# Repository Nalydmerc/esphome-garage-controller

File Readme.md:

### ESPHome Garage Door Controller

I am a forgetful man. I forget to close the garage door. My wife gets frustrated that I forget to close the garage door. I may or may not get slightly banned from the garage due to leaving the garage door open too many times after leaving for work. So, I do what any sensible man would do. I offload my responsibilities to technology, of course.

The device uses an ESP8266 running ESPHome to connect to HomeAssistant and do garage door things. I used a hall effect sensor to detect if each door was open or closed, but you could use any contact that opens/closes depending on the state of the door. To open and close the doors, I just wired in a relay in parallel with each button. YMMV, but for mine this did mean I had to physically disassemble each button and solder extra wires onto the PCB.

This project was designed to be cheap, as opposed to involved. You can build your own buck converters into your projects (I have in the past), but at the end of the day it's still cheaper to buy one of those cheap adjustable converters on aliexpress and call it a day. Sure there's 0.4V of switching noise, but the D1 Mini has a built in LDO anyway, as do most cheap development boards. ¯\\\_(ツ)\_/¯ A good project is one that is finished to spec, and my spec is that it works.

### Mechanical Assembly and Bill of Materials

.step files for a 3D printed enclosure are included in this project. The backplate uses M3 screws to mount the PCB, and M4 screws to attach the top. Other Non-PCB materials are as follows:

|Item | Qty|Link |
|--|--|--|
| Hall effect sensor |2| https://www.aliexpress.us/item/3256805925218267.html |
| Cabling || https://www.aliexpress.us/item/3256806428440404.html |
|Wire Ferrules (for crimping ends) || https://www.aliexpress.us/item/3256805075641713.html |
| Lever-nut connectors (love these) || https://www.aliexpress.us/item/3256803684080411.html |
| M3 Brass Inserts | 4 | https://www.aliexpress.us/item/3256803396040989.html |
| M3x5mm |4||
| M4 Brass Inserts | 4 | https://www.aliexpress.us/item/3256803396040989.html |
| M4x35mm |4||

### Manufacturing the PCB

If you want to make this PCB yourself, simply zip up the outputs folder and upload it to the PCB manufacturer of your choice. You can take the bill of materials CSV and upload it directly to digikey to create a cart with the needed components. Anything that doesn't have a digikey part number, I listed the relevant aliexpress product page.

### Random notes for myself

Reminder: Set switches to pins 5 and 4 to prevent them from toggling during startup. (esp8266s are weird. Never before have I had to deal with GPIOs just doing random things during the startup process.)

https://community.home-assistant.io/t/esp8266-relay-active-low-how-to-prevent-triggering-on-boot-or-reset-solved/88279/30
https://rabbithole.wwwdotorg.org/2017/03/28/esp8266-gpio.html

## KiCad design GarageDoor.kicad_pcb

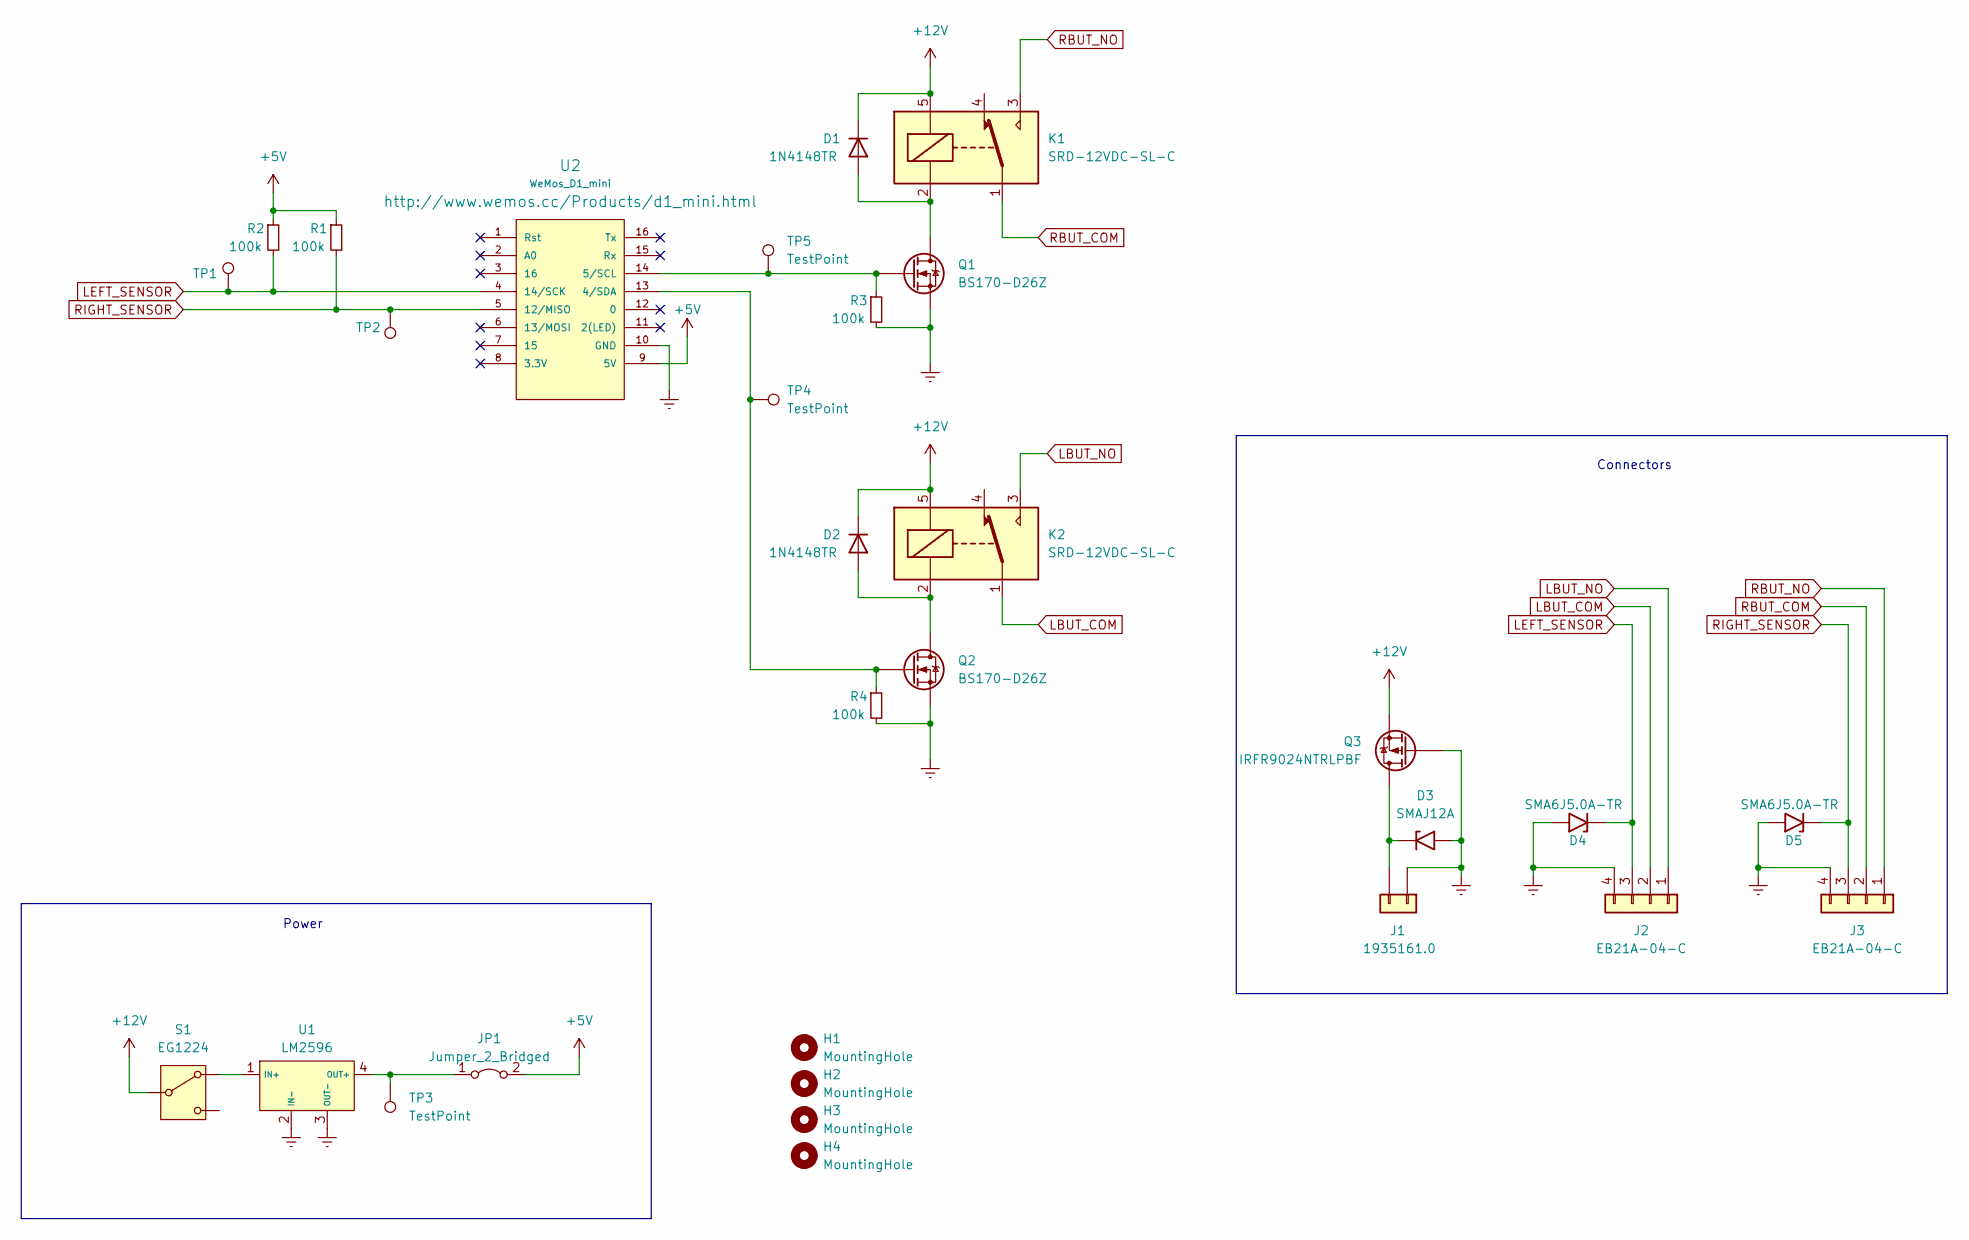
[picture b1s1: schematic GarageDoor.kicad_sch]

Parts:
D1, D2: 1N4148TR; D_DO-35_SOD27_P10.16mm_Horizontal; Digikey PN 1N4148FSCT-ND
D3: SMAJ12A; D_SMA_Handsoldering; Digikey PN SMAJ12ALFCT-ND
D4, D5: SMA6J5.0A-TR; D_SMA_Handsoldering; Digikey PN 497-5938-1-ND
H1, H2, H3, H4: MountingHole; MountingHole_3.2mm_M3
J1: 1935161.0; TerminalBlock_bornier-2_P5.08mm
J2, J3: EB21A-04-C; TerminalBlock_bornier-4_P5.08mm
JP1: Jumper_2_Bridged; PinHeader_1x02_P2.54mm_Vertical; Digikey PN S9337-ND
K1, K2: SRD-12VDC-SL-C; Relay_SPDT_Songle
Q1, Q2: BS170-D26Z; TO-92_Inline_Wide; Digikey PN BS170-D26ZCT-ND
Q3: IRFR9024NTRLPBF; TO-252-2; Digikey PN IRFR9024NTRLPBFCT-ND
R1, R2, R3, R4: 100k; R_Axial_DIN0207_L6.3mm_D2.5mm_P15.24mm_Horizontal
S1: EG1224; SW_E-Switch_EG1224_SPDT_Angled; Digikey PN EG2585-ND
TP1, TP2, TP3, TP4, TP5: TestPoint; TestPoint_Pad_1.5x1.5mm
U1: LM2596; LM2596Module
U2: WeMos_D1_mini; wemos-d1-mini-with-pin-header-and-connector

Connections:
+5V: JP1.2 (B), R1.1, R2.1, U2.9 (5V)
+12V: D1.1 (K), D2.1 (K), K1.5, K2.5, Q3.3 (S), S1.2 (B)
Earth: D3.2 (A2), D4.2 (A2), D5.2 (A2), J1.1, J2.4, J3.4, Q1.3 (S), Q2.3 (S), Q3.1 (G), R3.2, R4.2, U1.2 (IN-), U1.3 (OUT-), U2.10 (GND)
LBUT_COM: J2.2, K2.1
LBUT_NO: J2.1, K2.3
LEFT_SENSOR: D4.1 (A1), J2.3, R2.2, TP1.1, U2.4 (14/SCK)
unnamed: D1.2 (A), K1.2, Q1.1 (D)
unnamed: D2.2 (A), K2.2, Q2.1 (D)
unnamed: D3.1 (A1), J1.2, Q3.2 (D)
unnamed: JP1.1 (A), TP3.1, U1.4 (OUT+)
unnamed: Q1.2 (G), R3.1, TP5.1, U2.14 (5/SCL)
unnamed: Q2.2 (G), R4.1, TP4.1, U2.13 (4/SDA)
unnamed: S1.3 (A), U1.1 (IN+)
RBUT_COM: J3.2, K1.1
RBUT_NO: J3.1, K1.3
RIGHT_SENSOR: D5.1 (A1), J3.3, R1.2, TP2.1, U2.5 (12/MISO)

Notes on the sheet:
Connectors
Power

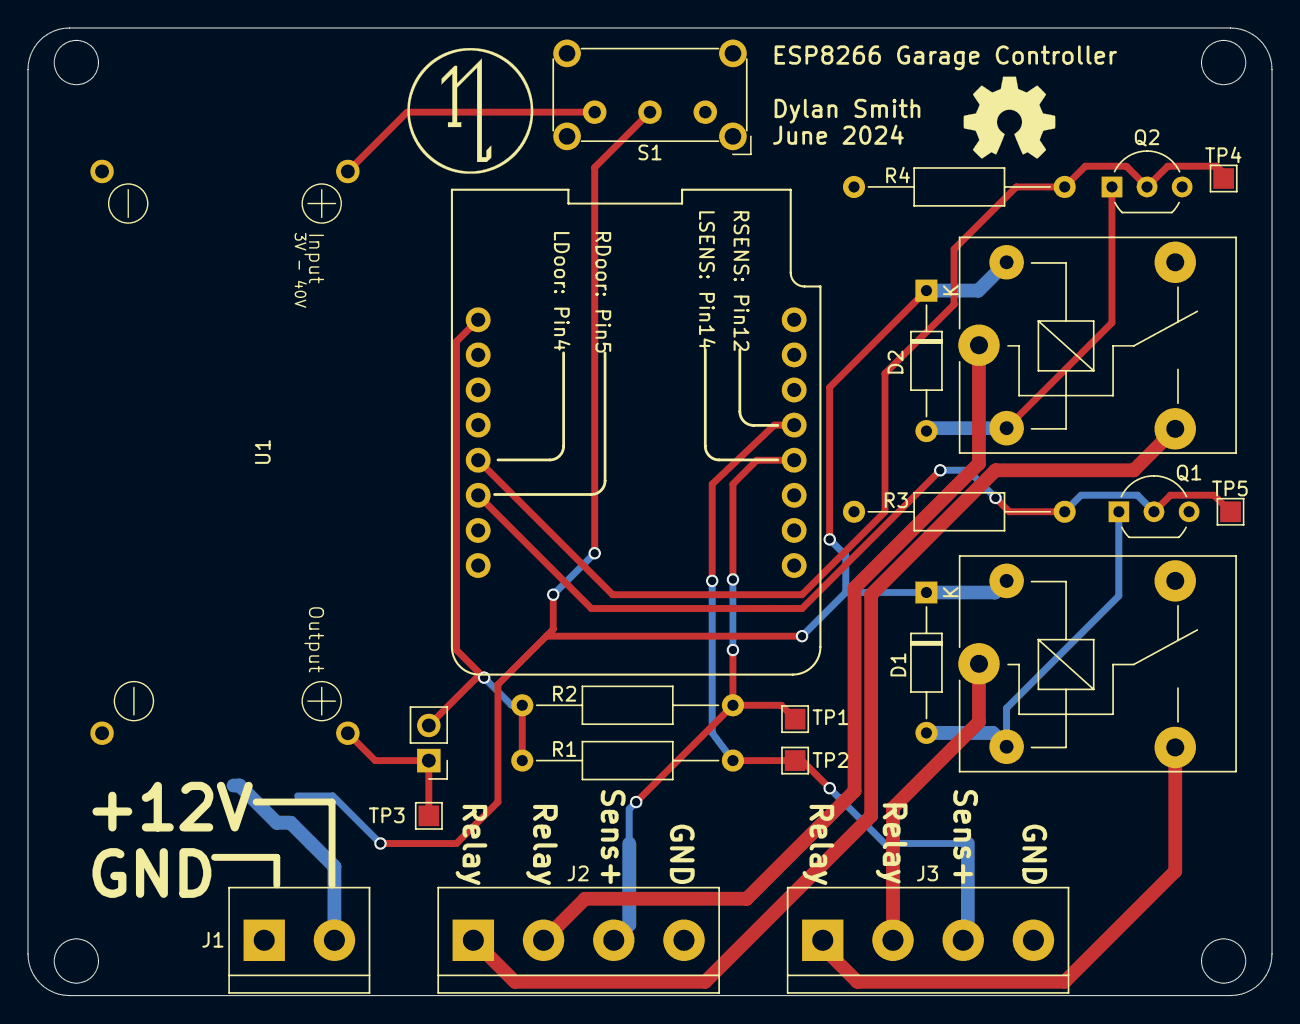
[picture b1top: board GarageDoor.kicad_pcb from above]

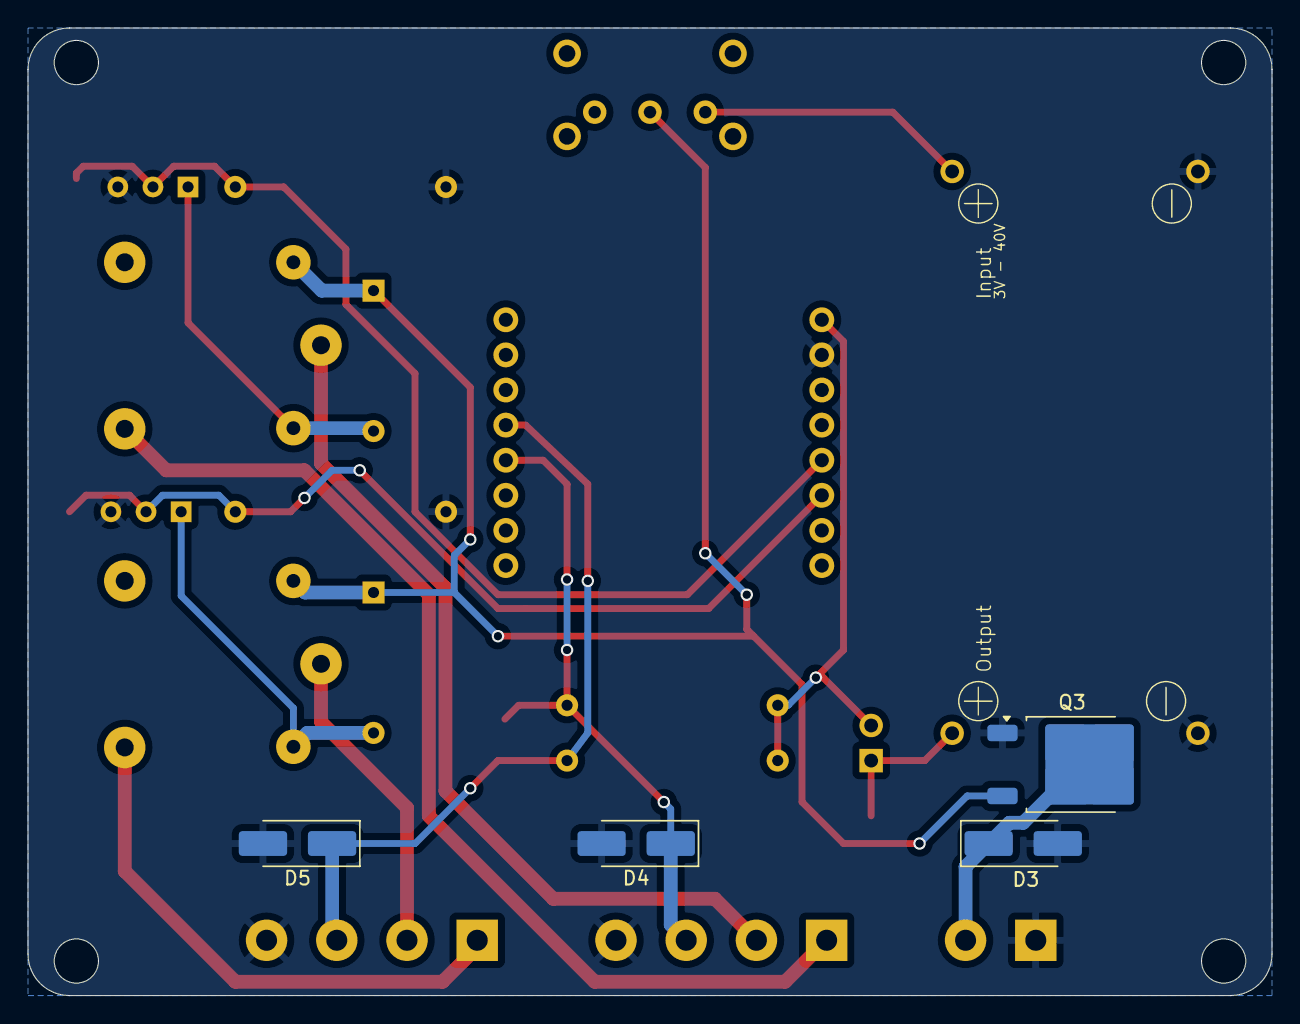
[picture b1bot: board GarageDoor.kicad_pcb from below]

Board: 2 copper layers, 90.0 x 70.0 mm, 30 parts (4 on the bottom side), 16 nets.

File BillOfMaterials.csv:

"Reference","Value","Footprint","Qty","DNP","Digikey PN","PN"
"D1,D2","1N4148TR","Diode_THT:D_DO-35_SOD27_P10.16mm_Horizontal","2","","1N4148FSCT-ND","DIO-004"
"D3","SMAJ12A","Diode_SMD:D_SMA_Handsoldering","1","","SMAJ12ALFCT-ND","DIO-014"
"D4,D5","SMA6J5.0A-TR","Diode_SMD:D_SMA_Handsoldering","2","","497-5938-1-ND","DIO-011"
"H1,H2,H3,H4","MountingHole","MountingHole:MountingHole_3.2mm_M3","4","","",""
"J1","1935161.0","TerminalBlock:TerminalBlock_bornier-2_P5.08mm","1","","https://www.aliexpress.us/item/3256805408760426.html","CON-005"
"J2,J3","EB21A-04-C","TerminalBlock:TerminalBlock_bornier-4_P5.08mm","2","","https://www.aliexpress.us/item/3256805408760426.html",""
"JP1","Jumper_2_Bridged","Connector_PinHeader_2.54mm:PinHeader_1x02_P2.54mm_Vertical","1","","S9337-ND",""
"K1,K2","SRD-12VDC-SL-C","000-Footprints:Relay_SPDT_Songle","2","","https://www.aliexpress.us/item/3256802839040760.html",""
"Q1,Q2","BS170-D26Z","Package_TO_SOT_THT:TO-92_Inline_Wide","2","","BS170-D26ZCT-ND","FET-002"
"Q3","IRFR9024NTRLPBF","Package_TO_SOT_SMD:TO-252-2","1","","IRFR9024NTRLPBFCT-ND","FET-007"
"R1,R2,R3,R4","100k","Resistor_THT:R_Axial_DIN0207_L6.3mm_D2.5mm_P15.24mm_Horizontal","4","","",""
"S1","EG1224","000-Footprints:SW_E-Switch_EG1224_SPDT_Angled","1","","EG2585-ND","MISC-006"
"TP1,TP2,TP3,TP4,TP5","TestPoint","TestPoint:TestPoint_Pad_1.5x1.5mm","5","","",""
"U1","LM2596","000-Footprints:LM2596Module","1","","https://www.aliexpress.us/item/3256804718557368.html","MISC-009"
"U2","WeMos_D1_mini","000-Footprints:wemos-d1-mini-with-pin-header-and-connector","1","","https://www.aliexpress.us/item/3256805831695231.html",""

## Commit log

2024-06-01 Initial commit.
2024-06-02 Connect unused pins to ground.
2024-06-02 Move right sensor to pin 12 instead of 16, because that breaks everything for some reason and you're apparently just supposed to know that.
2024-06-04 Add documentation.
2024-06-04 Oops, left a password in there. Don't worry I changed it. ;)
2024-06-04 Added note about esp8266 LED
2024-06-04 Minor silkscreen change
2024-06-14 Correct silkscreen. Update to Kicad 8.
